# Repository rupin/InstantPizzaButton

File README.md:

# InstantPizzaButton
Camp At CuriosityGym

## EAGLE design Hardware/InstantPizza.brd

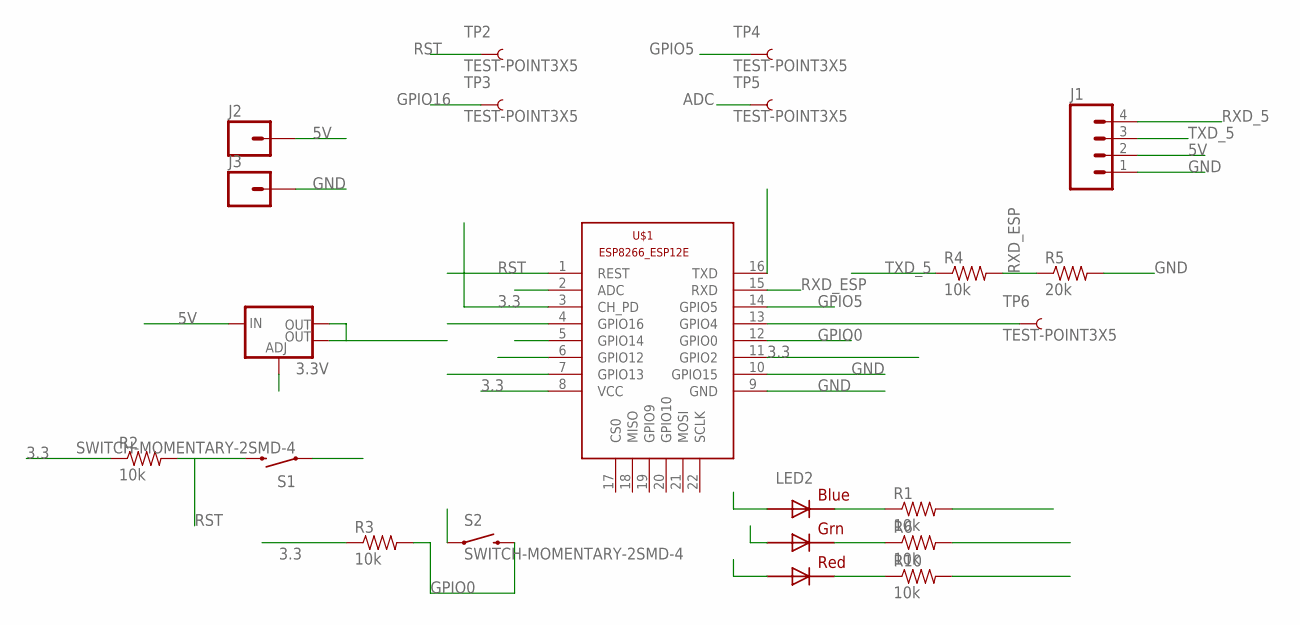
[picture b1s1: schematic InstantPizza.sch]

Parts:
3.3V: V_REG_LM1117SOT223; SOT223
J1: M04SMD; 1X04-SMD
J2, J3: M01SMD; LUXEON-PAD
LED2: RGBLED5050
R1, R2, R3, R4, R6, R10: 10k; 1206
R5: 20k; 1206
S1, S2: SWITCH-MOMENTARY-2SMD-4; TACTILE_SWITCH_TALL
TP2, TP3, TP4, TP5, TP6: TEST-POINT3X5; PAD.03X.05
U$1: ESP8266-12EESP8266-ESP12E; ESP8266-ESP12E

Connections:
3.3: 3.3V.2 (OUT), 3.3V.4 (OUT), R2.1, R3.1, U$1.3 (CH_PD), U$1.8 (VCC), U$1.11 (GPIO2)
5V: 3.3V.3 (IN), J1.2, J2.P$1
ADC: TP5.P$1, U$1.2 (ADC)
BLUE: LED2.3 (BLUE_A), U$1.5 (GPIO14)
GND: 3.3V.1 (ADJ), J1.1, J3.P$1, R1.2, R5.2, R6.2, R10.2, S1.A2 (1), S2.A2 (1), U$1.9 (GND), U$1.10 (GPIO15)
GPIO0: R3.2, S2.B2 (2), U$1.12 (GPIO0)
GPIO5: TP4.P$1, U$1.14 (GPIO5)
GPIO16: TP3.P$1, U$1.4 (GPIO16)
GREEN: LED2.1 (GREEN_A), U$1.7 (GPIO13)
unnamed: TP6.P$1, U$1.13 (GPIO4)
unnamed: LED2.6 (GREEN_C), R6.1
unnamed: LED2.4 (BLUE_C), R1.1
unnamed: LED2.5 (RED_C), R10.1
RED: LED2.2 (RED_A), U$1.6 (GPIO12)
RST: R2.2, S1.B2 (2), TP2.P$1, U$1.1 (REST)
RXD_5: J1.4, U$1.16 (TXD)
RXD_ESP: R4.2, R5.1, U$1.15 (RXD)
TXD_5: J1.3, R4.1

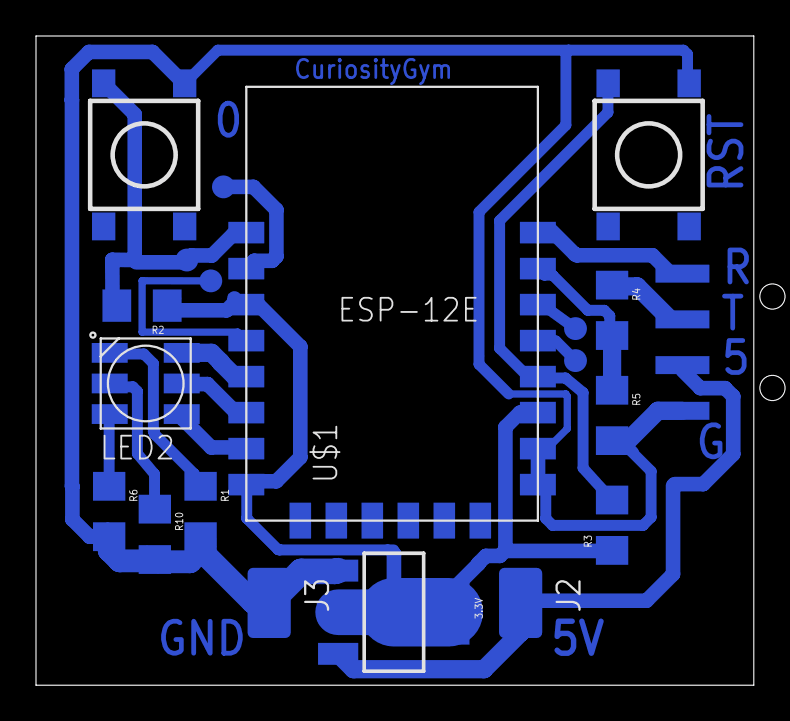
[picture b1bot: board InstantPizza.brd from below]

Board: 2 copper layers, 39.9 x 36.1 mm, 20 parts (20 on the bottom side), 18 nets.

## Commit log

2016-04-18 Seperated Toner Transfer and PCB Manufacturing

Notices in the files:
parts and their libraries:
SparkFun-PowerIC: Licensing: Creative Commons ShareAlike 4.0 International - https://creativecommons.org/licenses/by-sa/4.0
